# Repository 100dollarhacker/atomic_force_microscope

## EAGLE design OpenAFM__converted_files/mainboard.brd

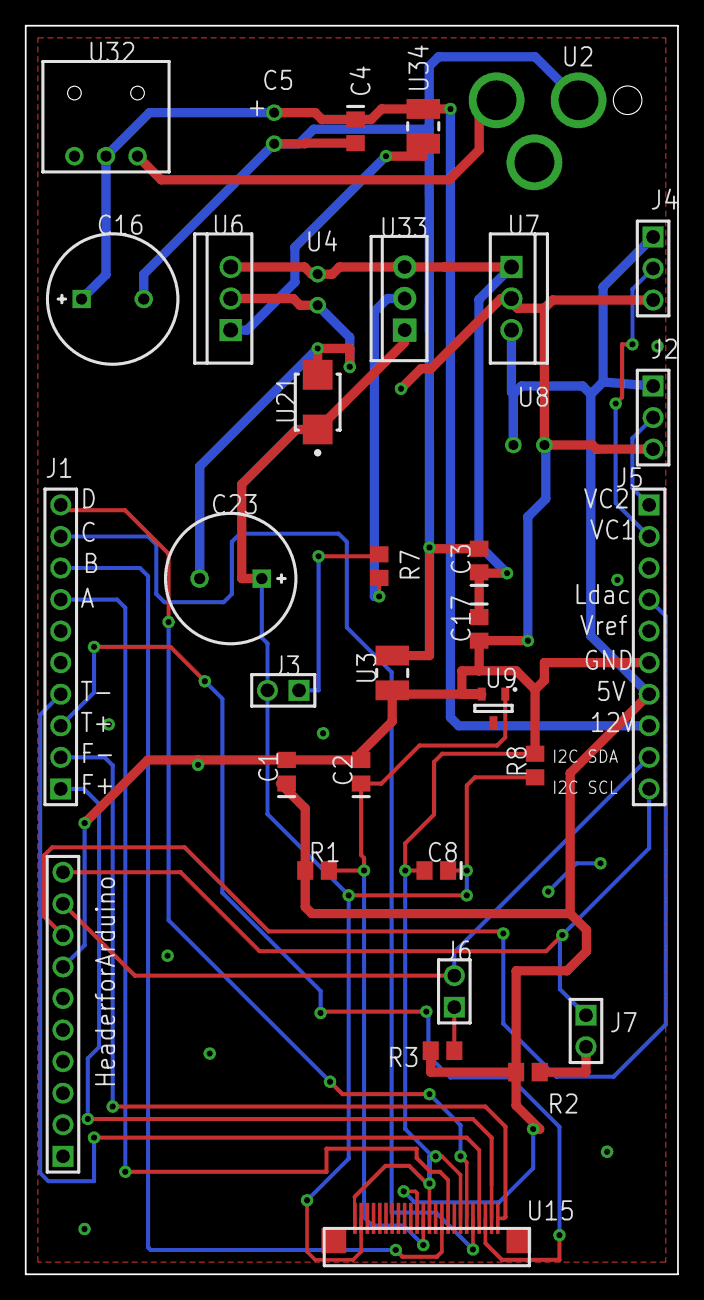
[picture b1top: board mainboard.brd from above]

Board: 2 copper layers, 52.5 x 100.5 mm, 34 parts (0 on the bottom side), 26 nets.

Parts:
C1, C3: 1u; CAP_0805
C2: 0u1; CAP_0805
C4: 1u; CAP_0805_C4
C5: 10UF CAP; CAPR-2.5/6.3h11
C8: 0u1; CAP_0805_C8
C16: 220UF CAP; CAPPR-5/10.5h14
C17: 1u; CAP_0805_C8
C23: 220UF CAP; CAPPR-5/10.5h14_C23
HeaderforArduino: 1-644456-0; HDR-1x10T/2.54/25x2_HeaderforArduino
J1: TVS3V5; HDR-1x10T/2.54/25x2
J2, J4: 644456-3; HDR-1x3T/2.54/7x2
J3: 90131-0121; HDR-2x1T/2.54x2.54/3x5
J5: 1-644456-0; HDR-1x10T/2.54/25x2_J5
J6: 90131-0121; HDR-2x1T/2.54x2.54/3x5_J6
J7: 90131-0121; HDR-2x1T/2.54x2.54/3x5_J7
R1: 1k; RES_0805
R2: 4k7; RES_0805_R2
R3: 4k7; RES_0805_R3
R7: 20R; RES_0805_R7
R8: 500k; RES_0805_R8
U2: DCJACK2.1MM; DCJack2.1mm
U3: 2A,45ohm; RES_1210
U4: 10UF CAP; CAPR-2.5/6.3h11
U6: L7809CV; TO-220V
U7: L7805CV; TO-220V_U7
U8: 10UF CAP; CAPR-2.5/6.3h11_U8
U9: 2.048V ref; SOT23
U15: SF-HD65 CONNECTOR; 24Pin_Flex_.5mm_Pitch
U21: TVS3V5; SMB
U32: SPSWITCH; SPswitch
U33: LM317T; TO-220
U34: 2A,45ohm; RES_1210_U34

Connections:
2V1: C2.1, R1.2, U9.1, U15.13
5V: C1.1, J2.1, J4.1, J5.7, R1.1, R2.2, R3.2, U7.2, U8.1, U15.14
9V: C3.1, C17.1, U4.1, U6.2, U7.1, U33.3
GND: C1.2, C2.2, C8.2, C17.2, C23.2, HeaderforArduino.7, J2.3, J4.3, J5.6, R8.1, U3.1, U4.2, U6.3, U7.3, U8.2, U9.2, U15.7, U15.12, U15.24, U21.2
GND_digi: C3.2, C4.2, C5.2, C16.2, U2.2, U3.2
Net_1: C4.1, C5.1, C16.1, J5.8, U32.2, U34.1
Net_4: J1.7, U15.9
Net_5: J1.8, U15.10
Net_6: J1.9, U15.5
Net_7: J1.10, U15.6
Net_8: J1.2, U15.1
Net_9: J1.1, U15.2
Net_10: J1.3, U15.3
Net_11: J1.4, U15.4
Net_16: J3.1, R7.2
Net_17: R7.1, U33.2
Net_18: C8.1, C23.1, J3.2, R8.2, U15.23, U21.1, U33.1
Net_19: HeaderforArduino.10, J5.10, J7.1
Net_20: HeaderforArduino.9, J5.9, J6.2
Net_21: HeaderforArduino.8, J5.4
Net_22: J4.2, J5.2
Net_23: J2.2, J5.1
Net_24: J6.1, R3.1
Net_25: J7.2, R2.1
Net_65: U2.1, U32.1
Net_72: U6.1, U34.2

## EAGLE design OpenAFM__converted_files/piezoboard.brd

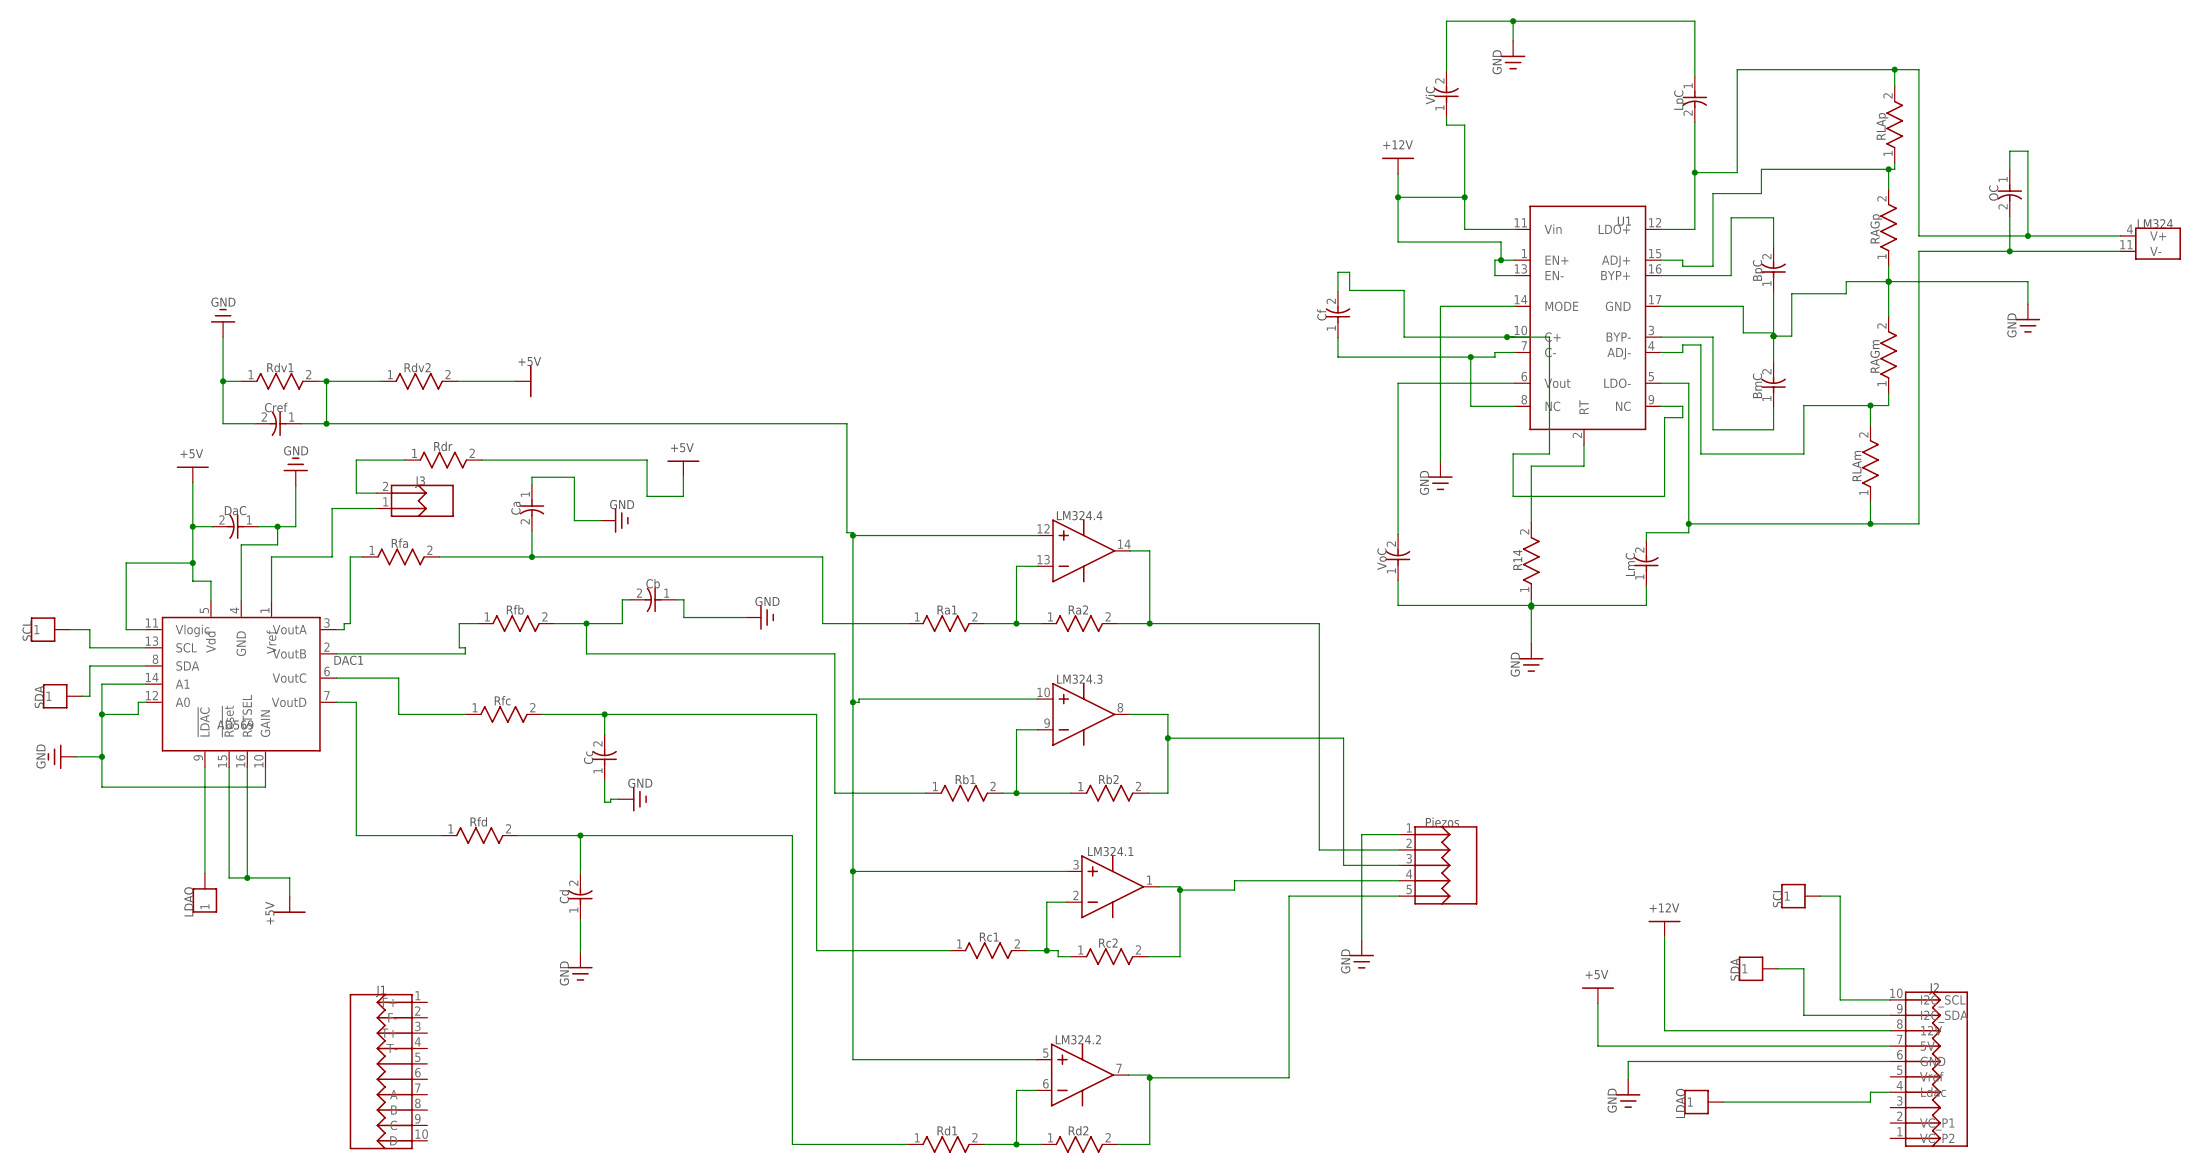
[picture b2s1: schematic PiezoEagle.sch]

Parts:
BmC: 10nF; CAP_0805
BpC: 10nF; CAP_0805
Ca: 3.2uF; CAP_0805
Cb: 3.2uF; CAP_0805
Cc: 3.2uF; CAP_0805
Cd: 3.2uF; CAP_0805
Cf: 1uF; CAP_0805
Cref: 3.2uF; CAP_0805
DAC1: AD5696RARUZ
DaC: 3.2uF; CAP_0805
J1: 1-644456-0; HDR-1X10T/2.54/25X2
J2: 1-644456-0_3; HDR-1X10T/2.54/25X2
J3: 90131-0121; HDR-2X1T/2.54X2.54/3X5
LM324: LM324AD; SOIC-14/150MIL
LmC: 10uF; CAP_0805
LpC: 10uF; CAP_0805
OC: 10uF; CAP_0805
Piezos: CON5M; HDR-1X5T/2.54/12X2
R14: 200k; RES_0402
RAGm: 100k; RES_0805
RAGp: 100k; RES_0805
RLAm: 800k; RES_0805
RLAp: 800k; RES_0805
Ra1: 5k; RES_0805
Ra2: 30k; RES_0805
Rb1: 5k; RES_0805
Rb2: 30k; RES_0805
Rc1: 5k; RES_0805
Rc2: 30k; RES_0805
Rd1: 5k; RES_0805
Rd2: 30k; RES_0805
Rdr: 10k; RES_0805
Rdv1, Rdv2: 10k; RES_0805
Rfa: 5k; RES_0805
Rfb: 5k; RES_0805
Rfc: 5k; RES_0805
Rfd: 5k; RES_0805
U1: LTC3260; LTC3260_MSOP
ViC: 10uF; CAP_0805
VoC: 10uF; CAP_0805

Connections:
5V: DAC1.5 (Vdd), DAC1.11 (Vlogic), DAC1.15 (!Reset), DAC1.16 (RSTSEL), DaC.2, J2.7 (5V), Rdr.2, Rdv2.2
Gnd: BmC.2, BpC.1, Ca.1, Cb.1, Cc.1, Cd.1, Cref.2, DAC1.4 (GND), DAC1.10 (GAIN), DAC1.12 (A0), DAC1.14 (A1), DaC.1, J2.6 (GND), LmC.1, LpC.1, Piezos.1, R14.1, RAGm.2, RAGp.1, Rdv1.1, U1.14 (MODE), U1.17 (GND), ViC.2, VoC.1
Net_0: LM324.13 (IN-), Ra1.2, Ra2.1
Net_1: LM324.4 (V+), LpC.2, OC.1, RLAp.2, U1.12 (LDO+); also elsewhere on the board
Net_2: Cref.1, LM324.3 (IN+), LM324.5 (IN+), LM324.10 (IN+), LM324.12 (IN+), Rdv1.2, Rdv2.1
Net_3: DAC1.3 (VoutA), Rfa.1; also elsewhere on the board
Net_4: Ca.2, Ra1.1, Rfa.2
Net_5: LM324.9 (IN-), Rb1.2, Rb2.1
Net_6: LM324.8 (OUT), Piezos.3, Rb2.2
Net_7: Cd.2, Rd1.1, Rfd.2
Net_8: LM324.2 (IN-), Rc1.2, Rc2.1
Net_9: LM324.1 (OUT), Piezos.4, Rc2.2
Net_10: DAC1.6 (VoutC), Rfc.1; also elsewhere on the board
Net_11: LM324.6 (IN-), Rd1.2, Rd2.1
Net_12: Cc.2, Rc1.1, Rfc.2
Net_13: DAC1.13 (SCL), J2.10 (I2C_SCL)
Net_14: DAC1.8 (SDA), J2.9 (I2C_SDA)
Net_15: DAC1.9 (!LDAC), J2.4 (Ldac)
Net_16: Cb.2, Rb1.1, Rfb.2
Net_17: Cf.1, U1.7 (C-), U1.8 (NC)
Net_18: Cf.2, U1.9 (NC), U1.10 (C+)
Net_19: LM324.14 (OUT), Piezos.2, Ra2.2
Net_20: J2.8 (12V), U1.1 (EN+), U1.11 (Vin), U1.13 (EN-), ViC.1
Net_21: LM324.11 (V-), LmC.2, OC.2, RLAm.1, U1.5 (LDO-); also elsewhere on the board
Net_22: U1.6 (Vout), VoC.2
Net_23: R14.2, U1.2 (RT)
Net_24: BpC.2, U1.16 (BYP+)
Net_25: DAC1.2 (VoutB), Rfb.1; also elsewhere on the board
Net_26: BmC.1, U1.3 (BYP-)
Net_28: RAGp.2, RLAp.1, U1.15 (ADJ+)
Net_30: RAGm.1, RLAm.2, U1.4 (ADJ-)
Net_31: LM324.7 (OUT), Piezos.5, Rd2.2
Net_32: DAC1.7 (VoutD), Rfd.1; also elsewhere on the board
Net_33: J3.2, Rdr.1
Net_34: DAC1.1 (Vref), J3.1

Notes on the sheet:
BmC
BpC
Cref
DaC
AD569
DAC1
LM324.1
LM324.2
LM324.3
LM324.4
LM324
LmC
LpC
GND
+12V
+5V
SCL
SDA
LDAQ
Piezos
R14
Ra1
Ra2
RAGm
RAGp
Rb1
Rb2
Rc1
Rc2
Rd1
Rd2
Rdr
Rdv1
Rdv2
Rfa
Rfb
Rfc
Rfd
RLAm
RLAp

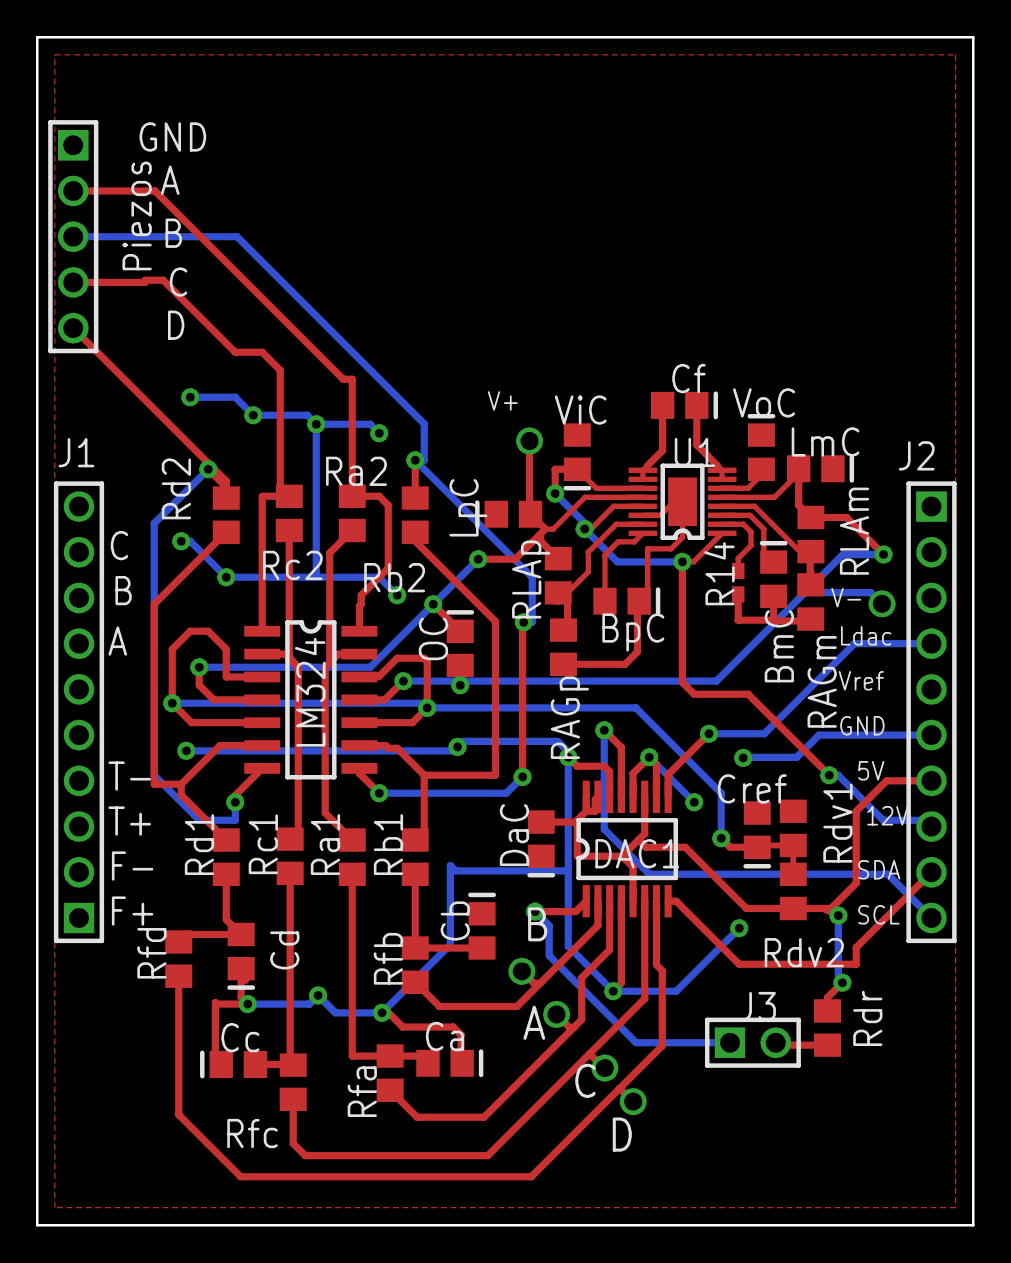
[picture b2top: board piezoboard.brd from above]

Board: 2 copper layers, 52.0 x 66.0 mm, 47 parts (0 on the bottom side), 35 nets.

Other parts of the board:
Pad1, Pad2, Pad3, Pad4, Pad5, Pad6: PAD; Pad

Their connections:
Net_1: Pad5.1; also elsewhere on the board
Net_3: Pad3.1; also elsewhere on the board
Net_10: Pad2.1; also elsewhere on the board
Net_21: Pad6.1; also elsewhere on the board
Net_25: Pad4.1; also elsewhere on the board
Net_32: Pad1.1; also elsewhere on the board

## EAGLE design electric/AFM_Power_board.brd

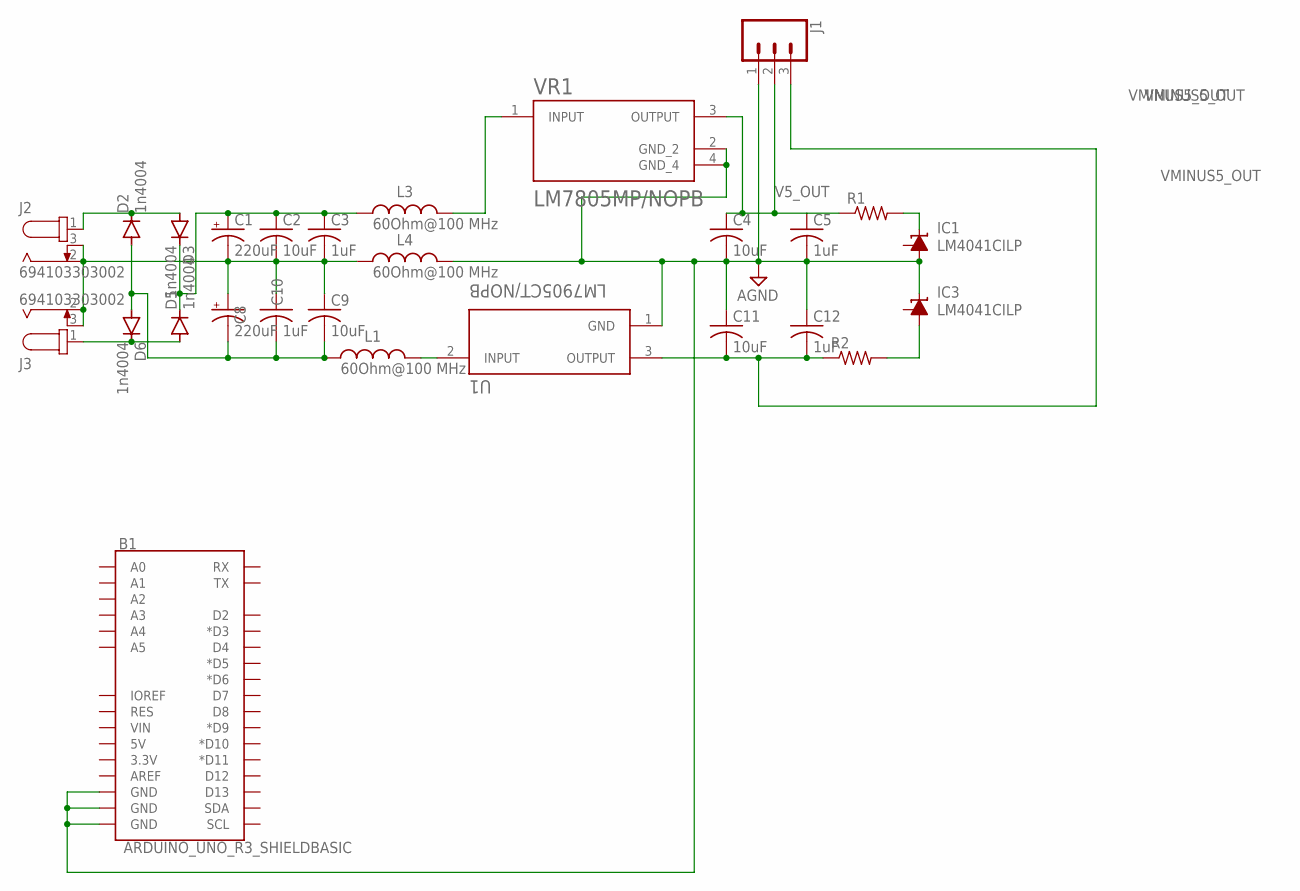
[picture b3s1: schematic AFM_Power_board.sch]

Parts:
B1: ARDUINO_UNO_R3_SHIELDBASIC; UNO_R3_SHIELD
C1, C8: 220uF; E5-8,5
C2, C4, C9, C11: 10uF; C050-024X044
C3, C5, C10, C12: 1uF; C050-024X044
D2, D3, D5, D6: 1n4004; SOD123
IC1, IC3: LM4041CILP; LP_O-PBCY-W3
J1: CONN_03LONGPADS; 1X03_LONGPADS
J2, J3: 694103303002
L1, L3, L4: 60Ohm@100 MHz; WE-CBF_0603_W2.2
R1, R2: R-US_0204/5; 0204/5
U1: LM7905CT/NOPB; TO254P1016X4575X1955-3
VR1: LM7805MP/NOPB; VREG_LM7805MP/NOPB

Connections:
AGND: B1.GND@0 (GND), B1.GND@1 (GND), B1.GND@2 (GND), C4.2, C5.2, C11.1, C12.1, IC1.3 (A), IC3.2 (C), J1.1, L4.2, U1.1 (GND), VR1.2 (GND_2), VR1.4 (GND_4)
GROUND: C1.-, C2.2, C3.2, C8.+, C9.1, C10.1, J2.2, J2.3, J3.2, J3.3, L4.1
unnamed: L3.2, VR1.1 (INPUT)
unnamed: L1.2, U1.2 (INPUT)
unnamed: IC1.2 (C), R1.2
unnamed: IC3.3 (A), R2.2
unnamed: D5.A, D6.C, J3.1
unnamed: C8.-, C9.2, C10.2, D2.A, D6.A, L1.1
unnamed: C1.+, C2.1, C3.1, D3.C, D5.C, L3.1
POWERP: D2.C, D3.A, J2.1
V5_OUT: C4.1, C5.1, J1.2, R1.1, VR1.3 (OUTPUT)
VMINUS5_OUT: C11.2, C12.2, J1.3, R2.1, U1.3 (OUTPUT)

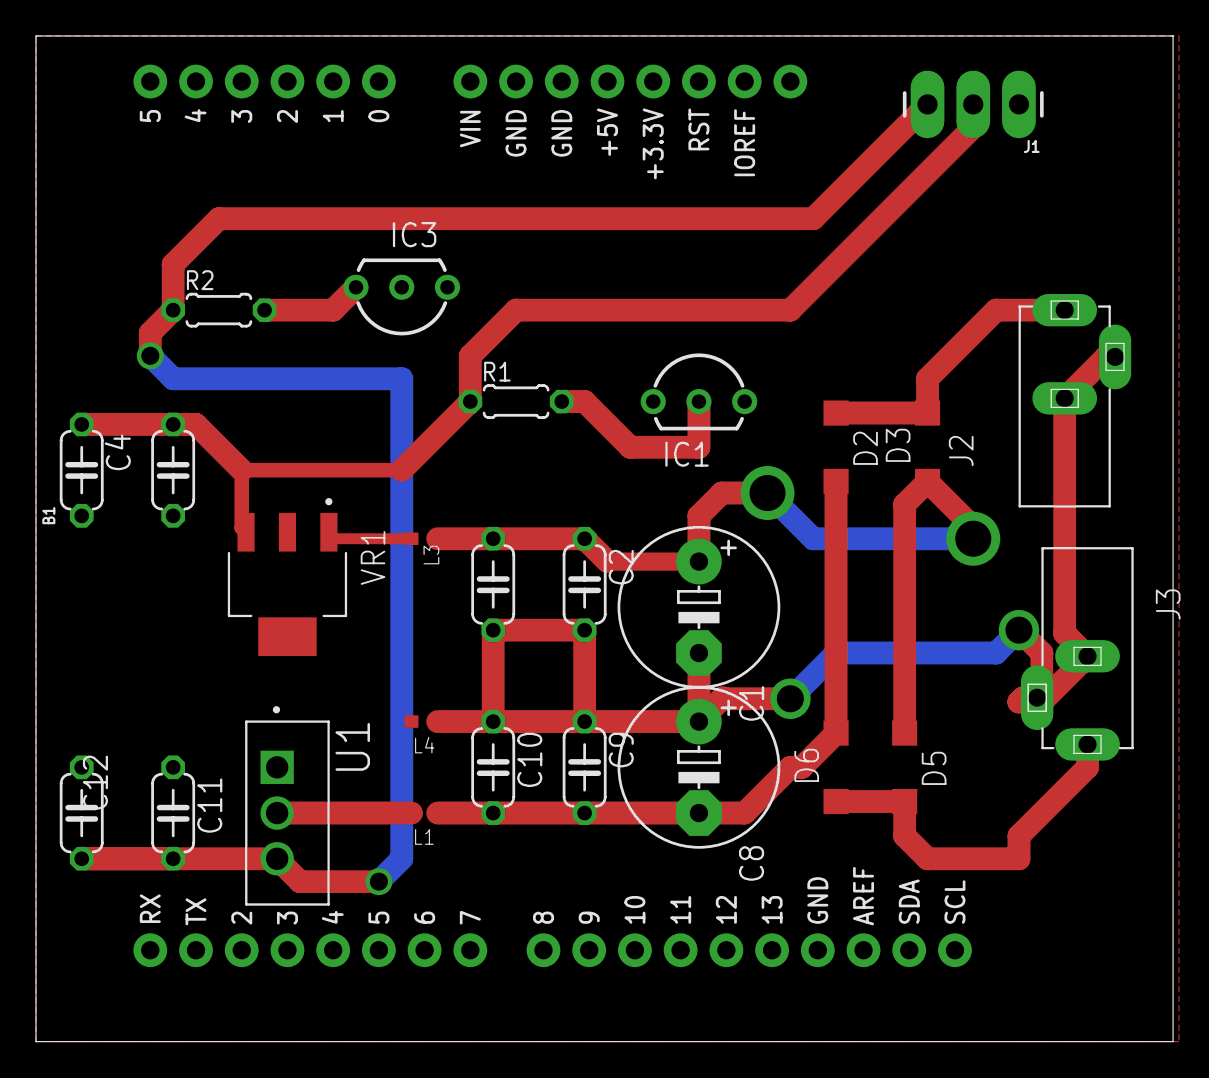
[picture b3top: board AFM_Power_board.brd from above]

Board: 2 copper layers, 63.2 x 55.9 mm, 27 parts (0 on the bottom side), 12 nets.

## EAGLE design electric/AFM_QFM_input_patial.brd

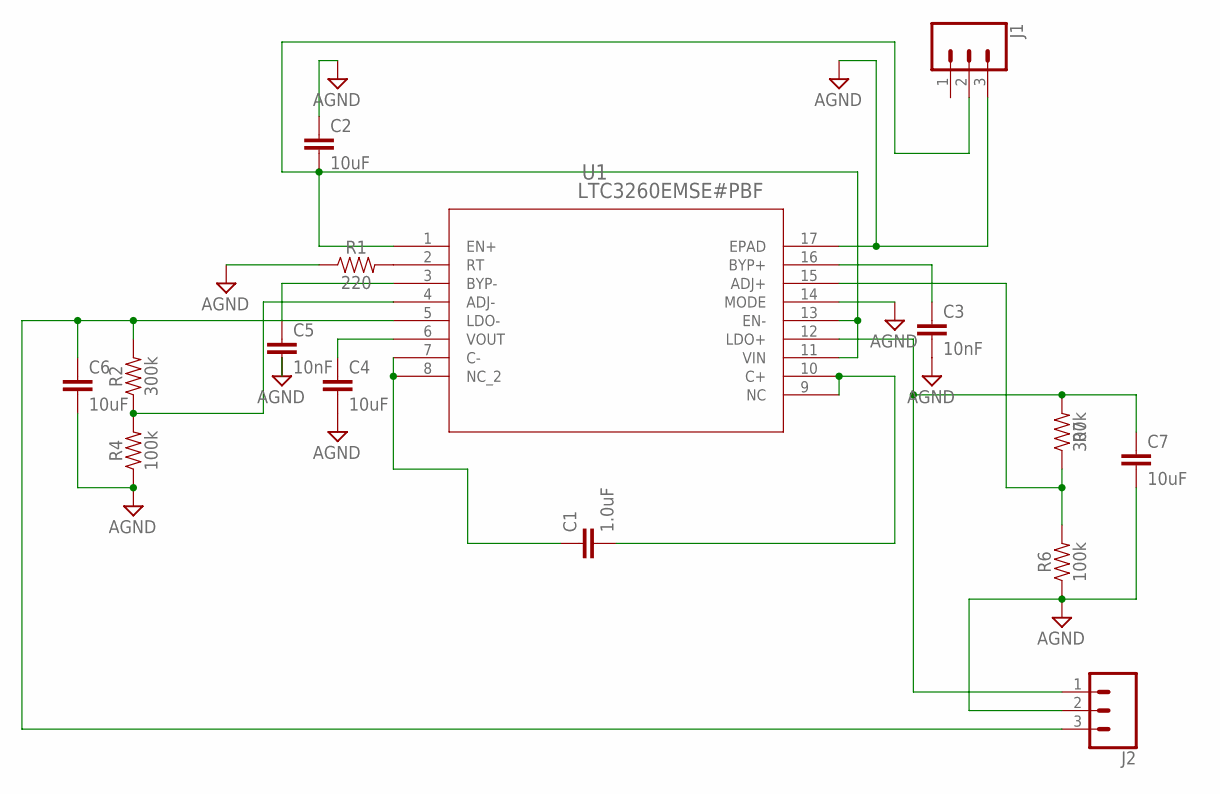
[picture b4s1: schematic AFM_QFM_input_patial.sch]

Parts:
C1: 1.0uF; 0805
C2, C4, C6, C7: 10uF; 0805
C3, C5: 10nF; 0603
J1, J2: CONN_03LONGPADS; 1X03_LONGPADS
R1: 220; 0603
R2, R7: 300k; 0603
R4, R6: 100k; 0603
U1: LTC3260EMSE#PBF; MSOP-16_MSE

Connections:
AGND: C2.1, C3.2, C4.2, C5.2, C6.2, C7.2, J1.3, J2.2, R1.1, R4.1, R6.1, U1.14 (MODE), U1.17 (EPAD)
unnamed: C5.1, U1.3 (BYP-)
unnamed: R1.2, U1.2 (RT)
unnamed: C1.1, U1.7 (C-), U1.8 (NC_2)
unnamed: C1.2, U1.9 (NC), U1.10 (C+)
unnamed: C2.2, J1.2, U1.1 (EN+), U1.11 (VIN), U1.13 (EN-)
unnamed: C3.1, U1.16 (BYP+)
unnamed: C4.1, U1.6 (VOUT)
unnamed: R2.1, R4.2, U1.4 (ADJ-)
unnamed: C6.1, J2.3, R2.2, U1.5 (LDO-)
unnamed: R6.2, R7.1, U1.15 (ADJ+)
unnamed: C7.1, J2.1, R7.2, U1.12 (LDO+)

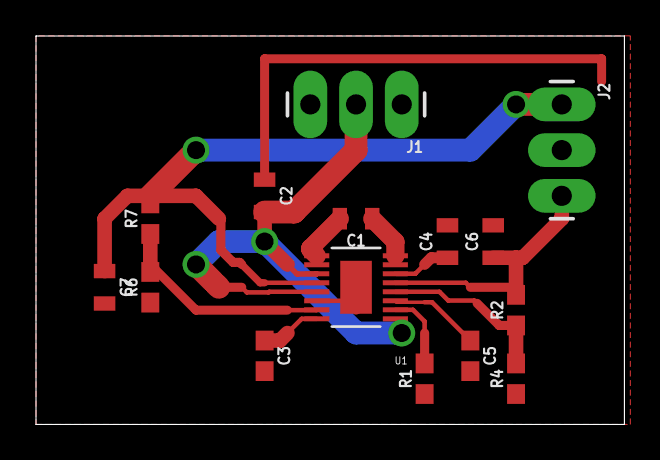
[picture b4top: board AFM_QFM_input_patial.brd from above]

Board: 2 copper layers, 32.7 x 21.6 mm, 15 parts (0 on the bottom side), 12 nets.

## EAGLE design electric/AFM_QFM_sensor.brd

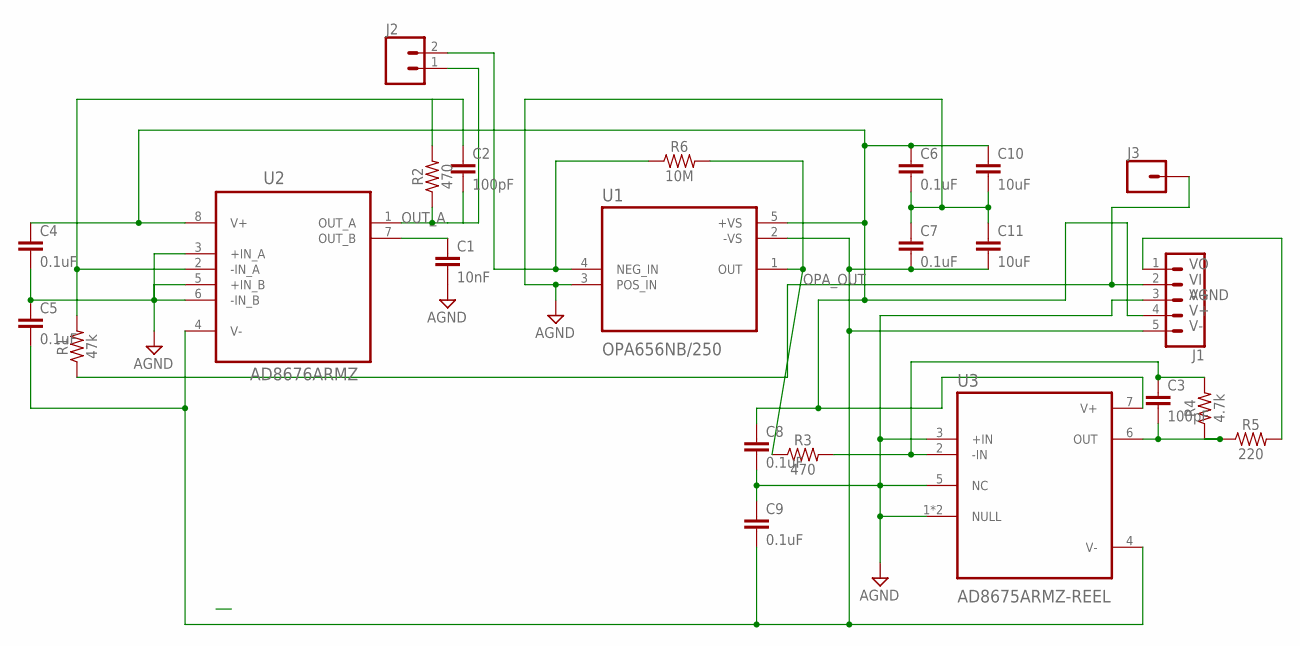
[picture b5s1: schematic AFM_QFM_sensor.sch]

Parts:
C1: 10nF; 0603
C2, C3: 100pF; 0603
C4, C5, C6, C7, C8, C9: 0.1uF; 0603
C10, C11: 10uF; 0805
J1: CONN_05PTH_LONGPADS; 1X05_LONGPADS
J2: CONN_02PTH3; 1X02_LONGPADS
J3: CONN_01PTH_LONGPAD; 1X01_LONGPAD
R1: 47k; 0603
R2, R3: 470; 0603
R4: 4.7k; 0603
R5: 220; 0603
R6: 10M; 0603
U1: OPA656NB/250; SOT95P280X145-5N
U2: AD8676ARMZ; SOP65P490X110-8N
U3: AD8675ARMZ-REEL; SOP65P490X110-8N

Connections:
AGND: C1.2, C4.2, C5.1, C6.2, C7.1, C8.2, C9.1, C10.2, C11.1, J1.3, U1.3 (POS_IN), U2.3 (+IN_A), U2.5 (+IN_B), U2.6 (-IN_B), U3.1 (NULL), U3.3 (+IN), U3.5 (NC), U3.8 (NULL)
unnamed: J2.2, R6.1, U1.4 (NEG_IN)
unnamed: C1.1, U2.7 (OUT_B)
unnamed: C2.1, R1.2, R2.2, U2.2 (-IN_A)
unnamed: C3.2, R4.1, R5.1, U3.6 (OUT)
OPA_OUT: C3.1, R3.1, R3.2, R4.2, R6.2, U1.1 (OUT), U3.2 (-IN)
OUT_A: C2.2, J2.1, R2.1, U2.1 (OUT_A)
V+: C4.1, C6.1, C8.1, C10.1, J1.4, U1.5 (+VS), U2.8 (V+), U3.7 (V+)
V-: C5.2, C7.2, C9.2, C11.2, J1.5, U1.2 (-VS), U2.4 (V-), U3.4 (V-)
VI: J1.2, J3.1, R1.1
VO: J1.1, R5.2

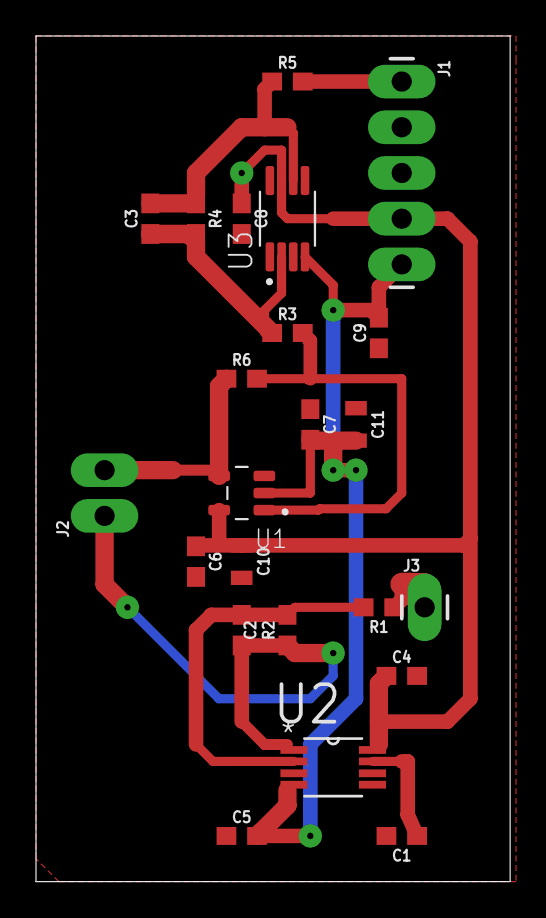
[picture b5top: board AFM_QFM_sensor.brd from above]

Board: 2 copper layers, 26.3 x 47.0 mm, 23 parts (0 on the bottom side), 11 nets.

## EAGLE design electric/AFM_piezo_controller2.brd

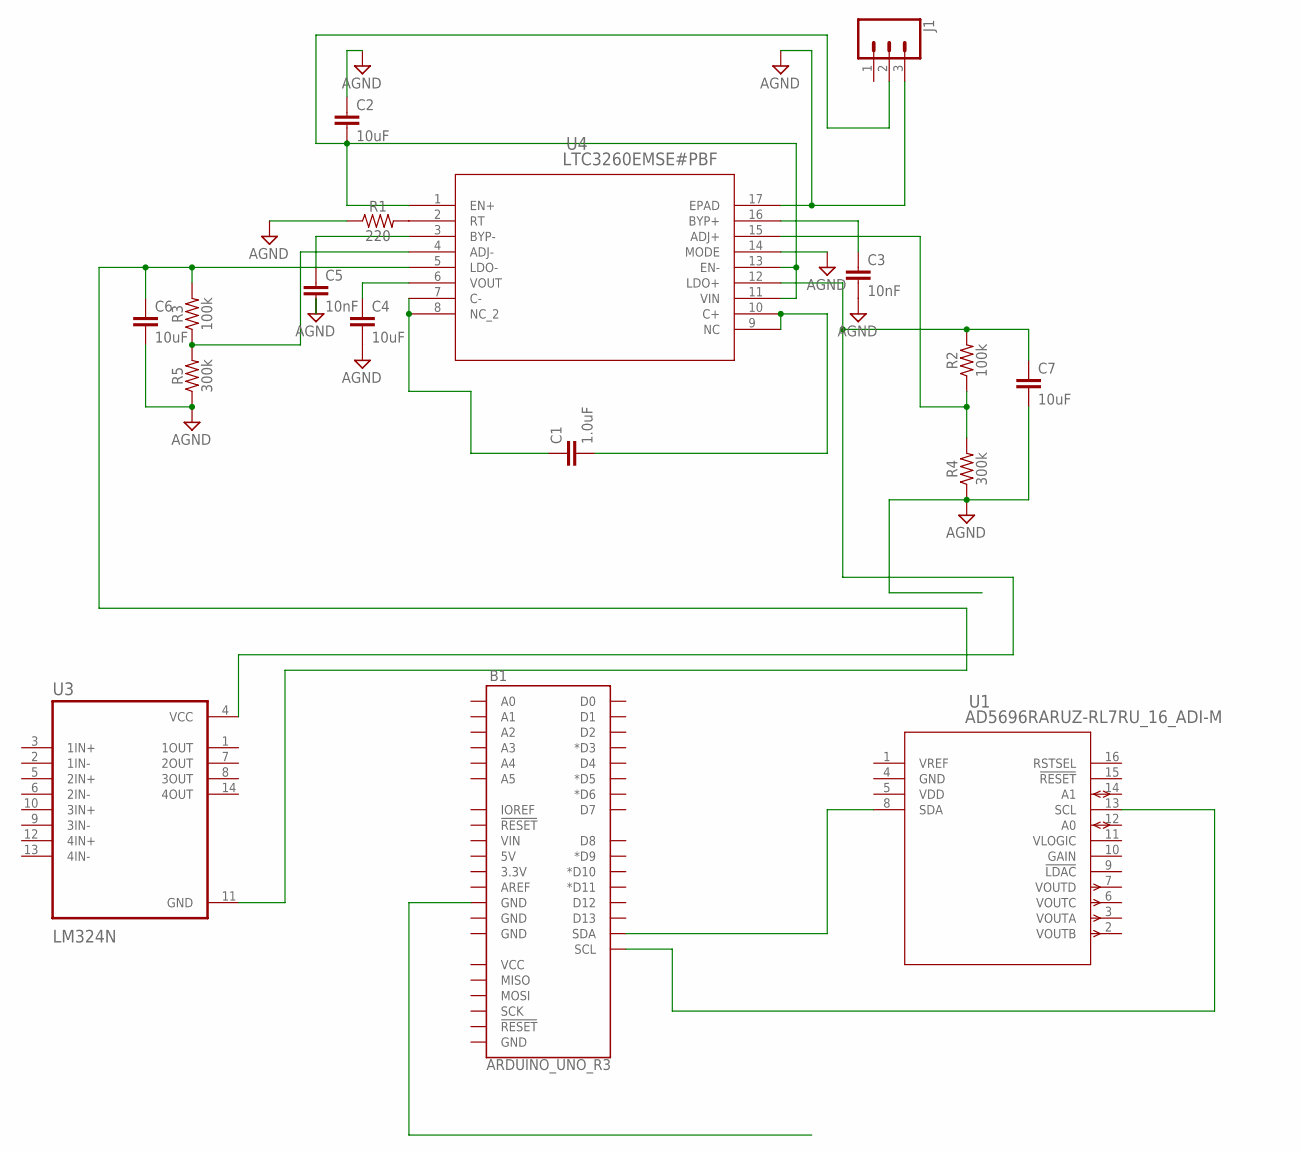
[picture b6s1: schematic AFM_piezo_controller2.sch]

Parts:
B1: ARDUINO_UNO_R3; ARDUINO_R3
C1: 1.0uF; 0805
C2, C4, C6, C7: 10uF; 0805
C3, C5: 10nF; 0603
J1: CONN_03LONGPADS; 1X03_LONGPADS
R1: 220; 0603
R2, R3: 100k; 0603
R4, R5: 300k; 0603
U1: AD5696RARUZ-RL7RU_16_ADI-M; RU_16_ADI-M
U3: LM324N; DIP794W45P254L1969H508Q14
U4: LTC3260EMSE#PBF; MSOP-16_MSE

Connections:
AGND: C2.1, C3.2, C4.2, C5.2, C6.2, C7.2, J1.3, R1.1, R4.1, R5.1, U4.14 (MODE), U4.17 (EPAD)
unnamed: C5.1, U4.3 (BYP-)
unnamed: R1.2, U4.2 (RT)
unnamed: C1.1, U4.7 (C-), U4.8 (NC_2)
unnamed: C1.2, U4.9 (NC), U4.10 (C+)
unnamed: C2.2, J1.2, U4.1 (EN+), U4.11 (VIN), U4.13 (EN-)
unnamed: C3.1, U4.16 (BYP+)
unnamed: C4.1, U4.6 (VOUT)
unnamed: R3.1, R5.2, U4.4 (ADJ-)
unnamed: B1.SDA, U1.8 (SDA)
unnamed: C6.1, R3.2, U3.11 (GND), U4.5 (LDO-)
unnamed: B1.SCL, U1.13 (SCL)
unnamed: R2.1, R4.2, U4.15 (ADJ+)
unnamed: C7.1, R2.2, U3.4 (VCC), U4.12 (LDO+)
VDD: U1.5 (VDD)
VLOGIC: U1.11 (VLOGIC)
VREF: U1.1 (VREF)

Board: 2 copper layers, 17 parts (0 on the bottom side), 14 nets, no tracks yet.

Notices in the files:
parts and their libraries:
Wurth_EMC Components_WE-CBF: Copyright: Würth Elektronik
SparkFun-Boards: Licensing: Creative Commons ShareAlike 4.0 International - https://creativecommons.org/licenses/by-sa/4.0
COPYRIGHT: Copyright (C) 2024 Ultra Librarian. All rights reserved.
